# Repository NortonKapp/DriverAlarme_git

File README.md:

# DriverAlarme_git
Drive em KiCad para informar o Alarme IntelBras do acionamento da Cerca Elétrica

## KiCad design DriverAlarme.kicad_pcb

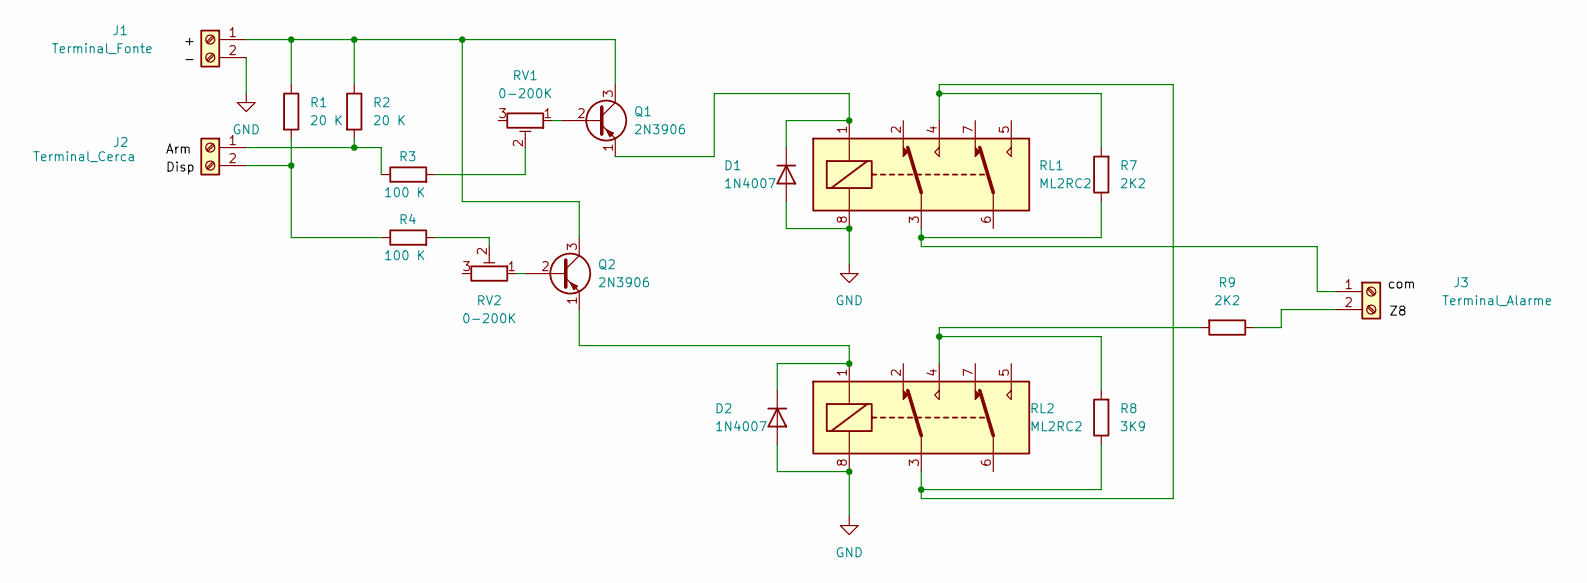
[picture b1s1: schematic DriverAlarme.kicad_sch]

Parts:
D1, D2: 1N4007; D_DO-41_SOD81_P10.16mm_Horizontal
J1: Terminal_Fonte; SolderWire-1sqmm_1x02_P5.4mm_D1.4mm_OD2.7mm
J2: Terminal_Cerca; SolderWire-1sqmm_1x02_P5.4mm_D1.4mm_OD2.7mm
J3: Terminal_Alarme; SolderWire-1sqmm_1x02_P5.4mm_D1.4mm_OD2.7mm
Q1, Q2: 2N3906; TO-92_Inline
R1, R2: 20 K; R_Axial_DIN0204_L3.6mm_D1.6mm_P7.62mm_Horizontal
R3, R4: 100 K; R_Axial_DIN0204_L3.6mm_D1.6mm_P7.62mm_Horizontal
R7, R9: 2K2; R_Axial_DIN0204_L3.6mm_D1.6mm_P7.62mm_Horizontal
R8: 3K9; R_Axial_DIN0204_L3.6mm_D1.6mm_P7.62mm_Horizontal
RL1, RL2: ML2RC2; Relay_DPDT_Omron_G2RL
RV1, RV2: 0-200K; Potentiometer_Bourns_3386F_Vertical

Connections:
GND: D1.2 (A), D2.2 (A), J1.2, RL1.8, RL2.8
unnamed: D1.1 (K), Q1.1 (E), RL1.1
unnamed: J1.1, Q1.3 (C), Q2.3 (C), R1.1, R2.1
unnamed: J2.1, R2.2, R3.1
unnamed: J3.1, R7.1, RL1.3
unnamed: J3.2, R9.1
unnamed: Q1.2 (B), RV1.1
unnamed: D2.1 (K), Q2.1 (E), RL2.1
unnamed: Q2.2 (B), RV2.1
unnamed: R3.2, RV1.2
unnamed: J2.2, R1.2, R4.1
unnamed: R4.2, RV2.2
unnamed: R7.2, R8.1, RL1.4, RL2.3
unnamed: R8.2, R9.2, RL2.4

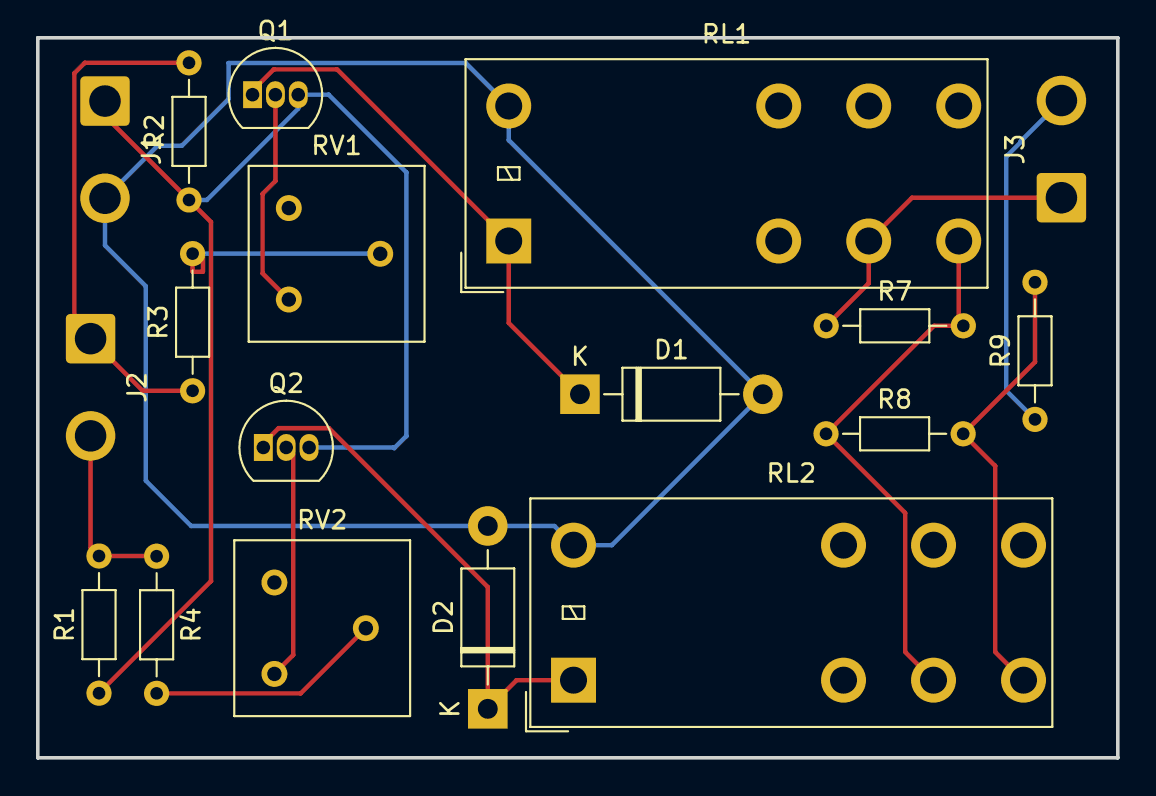
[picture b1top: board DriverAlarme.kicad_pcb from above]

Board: 2 copper layers, 60.0 x 40.0 mm, 18 parts (0 on the bottom side), 14 nets.

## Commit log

2022-09-09 README and gitignore
2022-09-09 Trimpot for adjust current over transistor
2022-09-09 Changed to wired conector
